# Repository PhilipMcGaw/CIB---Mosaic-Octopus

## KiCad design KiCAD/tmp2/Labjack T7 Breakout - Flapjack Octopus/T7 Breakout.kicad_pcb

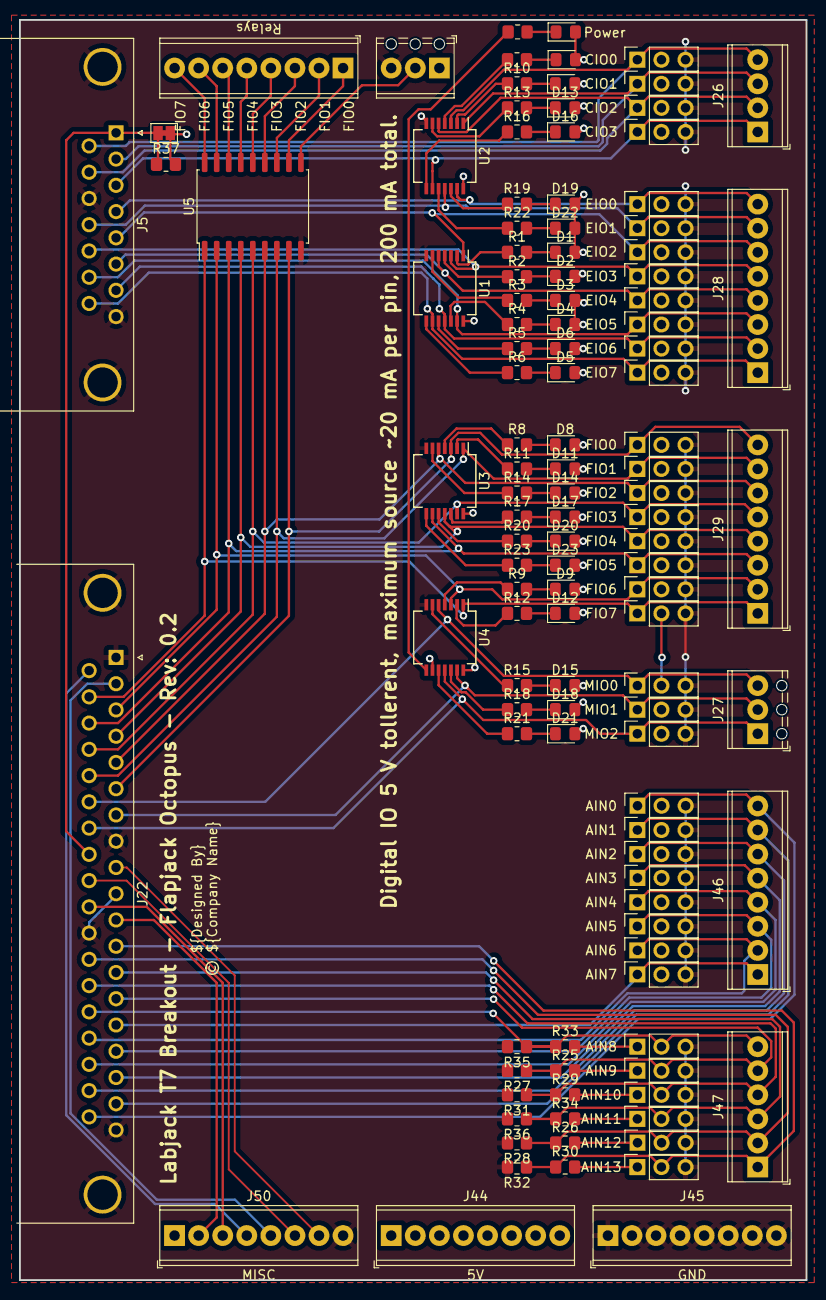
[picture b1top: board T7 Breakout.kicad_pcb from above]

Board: 2 copper layers, 83.0 x 133.0 mm, 117 parts (0 on the bottom side), 109 nets.

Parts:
D1: EIO2; LED_0805_2012Metric_Pad1.15x1.40mm_HandSolder
D2: EIO3; LED_0805_2012Metric_Pad1.15x1.40mm_HandSolder
D3: EIO4; LED_0805_2012Metric_Pad1.15x1.40mm_HandSolder
D4: EIO5; LED_0805_2012Metric_Pad1.15x1.40mm_HandSolder
D5: EIO7; LED_0805_2012Metric_Pad1.15x1.40mm_HandSolder
D6: EIO6; LED_0805_2012Metric_Pad1.15x1.40mm_HandSolder
D7: CIO0; LED_0805_2012Metric_Pad1.15x1.40mm_HandSolder
D8: FIO0; LED_0805_2012Metric_Pad1.15x1.40mm_HandSolder
D9: FIO6; LED_0805_2012Metric_Pad1.15x1.40mm_HandSolder
D10: CIO1; LED_0805_2012Metric_Pad1.15x1.40mm_HandSolder
D11: FIO1; LED_0805_2012Metric_Pad1.15x1.40mm_HandSolder
D12: FIO7; LED_0805_2012Metric_Pad1.15x1.40mm_HandSolder
D13: CIO2; LED_0805_2012Metric_Pad1.15x1.40mm_HandSolder
D14: FIO2; LED_0805_2012Metric_Pad1.15x1.40mm_HandSolder
D15: MIO0; LED_0805_2012Metric_Pad1.15x1.40mm_HandSolder
D16: CIO3; LED_0805_2012Metric_Pad1.15x1.40mm_HandSolder
D17: FIO3; LED_0805_2012Metric_Pad1.15x1.40mm_HandSolder
D18: MIO1; LED_0805_2012Metric_Pad1.15x1.40mm_HandSolder
D19: EIO0; LED_0805_2012Metric_Pad1.15x1.40mm_HandSolder
D20: FIO4; LED_0805_2012Metric_Pad1.15x1.40mm_HandSolder
D21: MIO2; LED_0805_2012Metric_Pad1.15x1.40mm_HandSolder
D22: EIO1; LED_0805_2012Metric_Pad1.15x1.40mm_HandSolder
D23: FIO5; LED_0805_2012Metric_Pad1.15x1.40mm_HandSolder
D24: Power; LED_0805_2012Metric_Pad1.15x1.40mm_HandSolder
J1: CIO0; PinSocket_1x03_P2.54mm_Vertical
J2: EIO2; PinSocket_1x03_P2.54mm_Vertical
J3: FIO0; PinSocket_1x03_P2.54mm_Vertical
J4: FIO6; PinSocket_1x03_P2.54mm_Vertical
J5: DA15; DSUB-15_Male_Horizontal_P2.77x2.84mm_EdgePinOffset9.90mm_Ho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
J6: CIO1; PinSocket_1x03_P2.54mm_Vertical
J7: EIO3; PinSocket_1x03_P2.54mm_Vertical
J8: FIO1; PinSocket_1x03_P2.54mm_Vertical
J9: FIO7; PinSocket_1x03_P2.54mm_Vertical
J10: CIO2; PinSocket_1x03_P2.54mm_Vertical
J11: EIO4; PinSocket_1x03_P2.54mm_Vertical
J12: FIO2; PinSocket_1x03_P2.54mm_Vertical
J13: MIO0; PinSocket_1x03_P2.54mm_Vertical
J14: CIO3; PinSocket_1x03_P2.54mm_Vertical
J15: EIO5; PinSocket_1x03_P2.54mm_Vertical
J16: FIO3; PinSocket_1x03_P2.54mm_Vertical
J17: MIO1; PinSocket_1x03_P2.54mm_Vertical
J18: EIO0; PinSocket_1x03_P2.54mm_Vertical
J19: EIO6; PinSocket_1x03_P2.54mm_Vertical
J20: FIO4; PinSocket_1x03_P2.54mm_Vertical
J21: MIO2; PinSocket_1x03_P2.54mm_Vertical
J22: DC37; DSUB-37_Male_Horizontal_P2.77x2.84mm_EdgePinOffset7.70mm_Ho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
J23: EIO7; PinSocket_1x03_P2.54mm_Vertical
J24: FIO5; PinSocket_1x03_P2.54mm_Vertical
J25: EIO1; PinSocket_1x03_P2.54mm_Vertical
J26: CIO; TerminalBlock_Phoenix_MPT-0,5-4-2.54_1x04_P2.54mm_Horizontal
J27: MIO; TerminalBlock_Phoenix_MPT-0,5-3-2.54_1x03_P2.54mm_Horizontal
J28: EIO; TerminalBlock_Phoenix_MPT-0,5-8-2.54_1x08_P2.54mm_Horizontal
J29: FIO; TerminalBlock_Phoenix_MPT-0,5-8-2.54_1x08_P2.54mm_Horizontal
J30: AIN0; PinSocket_1x03_P2.54mm_Vertical
J31: AIN1; PinSocket_1x03_P2.54mm_Vertical
J32: AIN2; PinSocket_1x03_P2.54mm_Vertical
J33: AIN3; PinSocket_1x03_P2.54mm_Vertical
J34: AIN6; PinSocket_1x03_P2.54mm_Vertical
J35: AIN9; PinSocket_1x03_P2.54mm_Vertical
J36: AIN12; PinSocket_1x03_P2.54mm_Vertical
J37: AIN4; PinSocket_1x03_P2.54mm_Vertical
J38: AIN7; PinSocket_1x03_P2.54mm_Vertical
J39: AIN10; PinSocket_1x03_P2.54mm_Vertical
J40: AIN13; PinSocket_1x03_P2.54mm_Vertical
J41: AIN5; PinSocket_1x03_P2.54mm_Vertical
J42: AIN8; PinSocket_1x03_P2.54mm_Vertical
J43: AIN11; PinSocket_1x03_P2.54mm_Vertical
J44: 5V; TerminalBlock_Phoenix_MPT-0,5-8-2.54_1x08_P2.54mm_Horizontal
J45: GND; TerminalBlock_Phoenix_MPT-0,5-8-2.54_1x08_P2.54mm_Horizontal
J46: AIN; TerminalBlock_Phoenix_MPT-0,5-8-2.54_1x08_P2.54mm_Horizontal
J47: AIN; TerminalBlock_Phoenix_MPT-0,5-6-2.54_1x06_P2.54mm_Horizontal
J48: External Supply; TerminalBlock_Phoenix_MPT-0,5-3-2.54_1x03_P2.54mm_Horizontal
J49: Relays; TerminalBlock_Phoenix_MPT-0,5-8-2.54_1x08_P2.54mm_Horizontal
J50: MISC; TerminalBlock_Phoenix_MPT-0,5-8-2.54_1x08_P2.54mm_Horizontal
JP1: 5 V connect; SolderJumper-2_P1.3mm_Bridged_Pad1.0x1.5mm
R1, R2, R3, R4, R5, R6, R7, R8, R9, R10, R11, R12, R13, R14, R15, R16, R17, R18, R19, R20, R21, R22, R23, R24, R27, R28, R31, R32, R35, R36, R37: 1k; R_0805_2012Metric_Pad1.20x1.40mm_HandSolder
R25, R26, R29, R30, R33, R34: 2k2; R_0805_2012Metric_Pad1.20x1.40mm_HandSolder
U1, U2, U3, U4: 74LS04; SSOP-14_5.3x6.2mm_P0.65mm
U5: ULN2803A; SOIC-18W_7.5x11.6mm_P1.27mm

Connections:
+5V: D1.2 (A), D2.2 (A), D3.2 (A), D4.2 (A), D5.2 (A), D6.2 (A), D7.2 (A), D8.2 (A), D9.2 (A), D10.2 (A), D11.2 (A), D12.2 (A), D13.2 (A), D14.2 (A), D15.2 (A), D16.2 (A), D17.2 (A), D18.2 (A), D19.2 (A), D20.2 (A), D21.2 (A), D22.2 (A), D23.2 (A), D24.2 (A), J1.2, J2.2, J3.2, J4.2, J6.2, J7.2, J8.2, J9.2, J10.2, J11.2, J12.2, J13.2, J14.2, J15.2, J16.2, J17.2, J18.2, J19.2, J20.2, J21.2, J23.2, J24.2, J25.2, J30.2, J31.2, J32.2, J33.2, J34.2, J37.2, J38.2, J41.2, J44.1, J44.2, J44.3, J44.4, J44.5, J44.6, J44.7, J44.8, J48.1, J50.1, JP1.2 (B), R37.2, U1.14 (VCC), U2.14 (VCC), U3.14 (VCC), U4.9, U4.14 (VCC)
+5V5_ISO_1: J5.1, J22.27, JP1.1 (A), R37.1
/10µA: J22.2, J50.5
/200µA: J22.20, J50.4
/AIN0: J22.37, J30.1, J46.8
/AIN1: J22.18, J31.1, J46.7
/AIN2: J22.36, J32.1, J46.6
/AIN3: J22.17, J33.1, J46.5
/AIN4: J22.35, J37.1, J46.4
/AIN5: J22.16, J41.1, J46.3
/AIN6: J22.34, J34.1, J46.2
/AIN7: J22.15, J38.1, J46.1
/AIN8: J22.33, J42.2, J47.6, R33.1, R35.1
/AIN9: J22.14, J35.2, J47.5, R25.1, R27.1
/AIN10: J22.32, J39.2, J47.4, R29.1, R31.1
/AIN11: J22.13, J43.2, J47.3, R34.1, R36.1
/AIN12: J22.31, J36.2, J47.2, R26.1, R28.1
/AIN13: J22.12, J40.2, J47.1, R30.1, R32.1
/CIO0: J1.1, J5.9, J26.4, U2.3
/CIO1: J5.2, J6.1, J26.3, U2.1
/CIO2: J5.10, J10.1, J26.2, U2.5
/CIO3: J5.3, J14.1, J26.1, U2.9
/DAC0: J22.11, J50.2
/DAC1: J22.29, J50.3
/EIO0: J5.4, J18.1, J28.8, U2.13
/EIO1: J5.12, J25.1, J28.7, U2.11
/EIO2: J2.1, J5.5, J28.6, U1.1
/EIO3: J5.13, J7.1, J28.5, U1.3
/EIO4: J5.6, J11.1, J28.4, U1.5
/EIO5: J5.14, J15.1, J28.3, U1.13
/EIO6: J5.7, J19.1, J28.2, U1.11
/EIO7: J5.15, J23.1, J28.1, U1.9
/FIO0: J3.1, J22.6, J29.8, U3.3, U5.8 (I8)
/FIO1: J8.1, J22.24, J29.7, U3.1, U5.7 (I7)
/FIO2: J12.1, J22.5, J29.6, U3.5, U5.6 (I6)
/FIO3: J16.1, J22.23, J29.5, U3.13, U5.5 (I5)
/FIO4: J20.1, J22.4, J29.4, U3.11, U5.4 (I4)
/FIO5: J22.22, J24.1, J29.3, U3.9, U5.3 (I3)
/FIO6: J4.1, J22.3, J29.2, U4.3, U5.2 (I2)
/FIO7: J9.1, J22.21, J29.1, U4.1, U5.1 (I1)
/MIO0: J13.1, J22.25, J27.3, U4.5
/MIO1: J17.1, J22.7, J27.2, U4.13
/MIO2: J21.1, J22.26, J27.1, U4.11
/VM+: J22.28, J50.6
/VM-: J22.9, J50.7
GND: J1.3, J2.3, J3.3, J4.3, J5.0 (PAD), J5.8, J5.11 (P111), J6.3, J7.3, J8.3, J9.3, J10.3, J11.3, J12.3, J13.3, J14.3, J15.3, J16.3, J17.3, J18.3, J19.3, J20.3, J21.3, J22.0 (PAD), J22.1, J22.8, J22.10, J22.19, J22.30, J23.3, J24.3, J25.3, J30.3, J31.3, J32.3, J33.3, J34.3, J35.3, J36.3, J37.3, J38.3, J39.3, J40.3, J41.3, J42.3, J43.3, J45.1, J45.2, J45.3, J45.4, J45.5, J45.6, J45.7, J45.8, J48.3, J50.8, R27.2, R28.2, R31.2, R32.2, R35.2, R36.2, U1.7 (GND), U2.7 (GND), U3.7 (GND), U4.7 (GND), U5.9 (GND)
unnamed: D1.1 (K), R1.2
unnamed: D2.1 (K), R2.2
unnamed: D3.1 (K), R3.2
unnamed: D4.1 (K), R4.2
unnamed: D5.1 (K), R6.2
unnamed: D6.1 (K), R5.2
unnamed: D7.1 (K), R7.2
unnamed: D8.1 (K), R8.2
unnamed: D9.1 (K), R9.2
unnamed: D10.1 (K), R10.2
unnamed: D11.1 (K), R11.2
unnamed: D12.1 (K), R12.2
unnamed: D13.1 (K), R13.2
unnamed: D14.1 (K), R14.2
unnamed: D15.1 (K), R15.2
unnamed: D16.1 (K), R16.2
unnamed: D17.1 (K), R17.2
unnamed: D18.1 (K), R18.2
unnamed: D19.1 (K), R19.2
unnamed: D20.1 (K), R20.2
unnamed: D21.1 (K), R21.2
unnamed: D22.1 (K), R22.2
unnamed: D23.1 (K), R23.2
unnamed: D24.1 (K), R24.2
unnamed: J35.1, R25.2
unnamed: J36.1, R26.2
unnamed: J39.1, R29.2
unnamed: J40.1, R30.2
unnamed: J42.1, R33.2
unnamed: J43.1, R34.2
unnamed: J48.2, U5.10 (COM)
unnamed: J49.1, U5.11 (O8)
unnamed: J49.2, U5.12 (O7)
unnamed: J49.3, U5.13 (O6)
unnamed: J49.4, U5.14 (O5)
unnamed: J49.5, U5.15 (O4)
unnamed: J49.6, U5.16 (O3)
unnamed: J49.7, U5.17 (O2)
unnamed: J49.8, U5.18 (O1)
unnamed: R1.1, U1.2
unnamed: R2.1, U1.4
unnamed: R3.1, U1.6
unnamed: R4.1, U1.12
unnamed: R5.1, U1.10
unnamed: R6.1, U1.8
unnamed: R7.1, U2.4
unnamed: R8.1, U3.4
unnamed: R9.1, U4.4
unnamed: R10.1, U2.2
unnamed: R11.1, U3.2
unnamed: R12.1, U4.2
unnamed: R13.1, U2.6
unnamed: R14.1, U3.6
unnamed: R15.1, U4.6
unnamed: R16.1, U2.8
unnamed: R17.1, U3.12
unnamed: R18.1, U4.12
unnamed: R19.1, U2.12
unnamed: R20.1, U3.10
unnamed: R21.1, U4.10
unnamed: R22.1, U2.10
unnamed: R23.1, U3.8
unnamed: R24.1, U4.8
